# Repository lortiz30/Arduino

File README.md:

Arduino
=======

This repository is for my personal  arduino work

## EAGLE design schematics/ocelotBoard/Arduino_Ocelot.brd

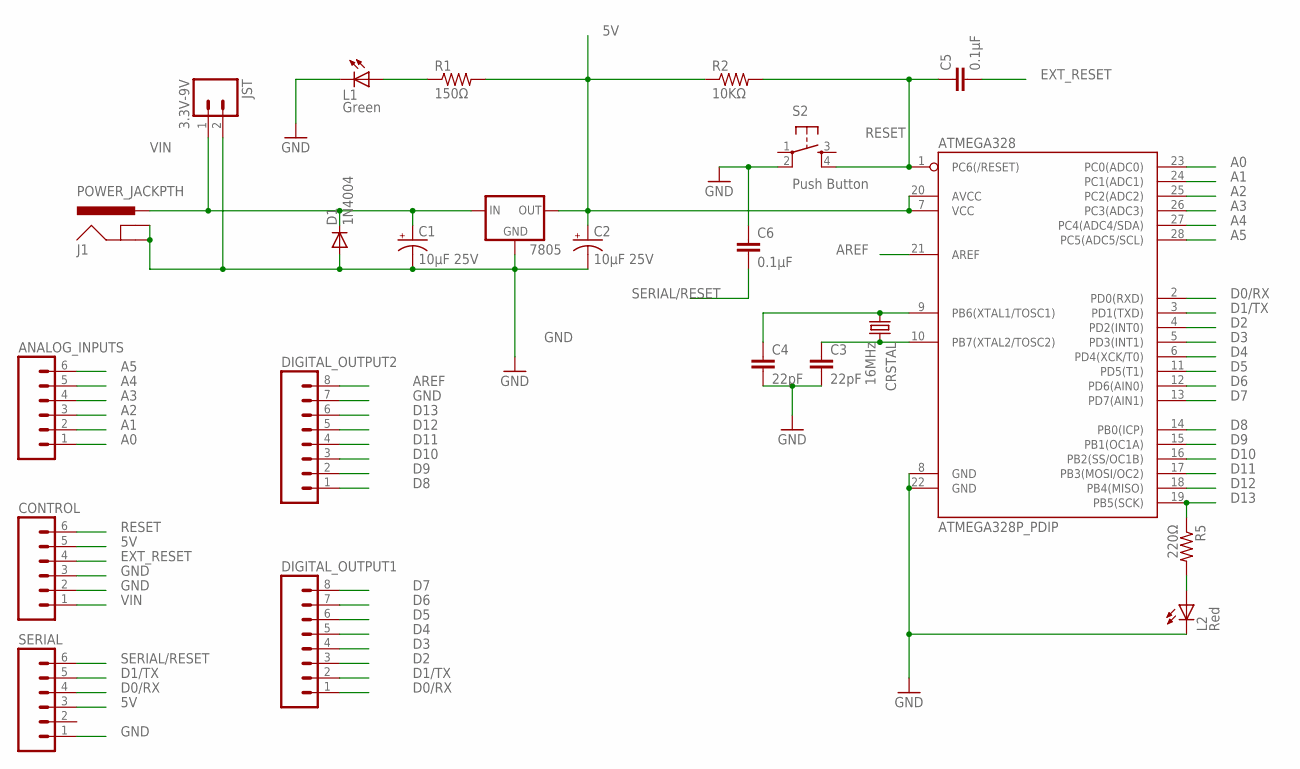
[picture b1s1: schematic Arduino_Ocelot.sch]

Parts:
7805: V_REG_78XXTO-92_UNTESTED; TO-92
ANALOG_INPUTS: M06FEMALE_LOCK; 1X06_FEMALE_LOCK.010
ATMEGA328: ATMEGA328P_PDIP; DIL28-3
C1, C2: 10µF 25V; CPOL-RADIAL-10UF-25V-KIT
C3, C4: 22pF; CAP-PTH-SMALL-KIT
C5, C6: 0.1µF; CAP-PTH-SMALL-KIT
CONTROL: M06FEMALE_LOCK; 1X06_FEMALE_LOCK.010
CRSTAL: 16MHz; HC49US
D1: 1N4004; DIODE-1N4001-KIT
DIGITAL_OUTPUT1, DIGITAL_OUTPUT2: M08NO_SILK; 1X08_NO_SILK
J1: POWER_JACKPTH; POWER_JACK_PTH
JST: 3.3V-9V; JST-2-PTH-VERT
L1: Green; LED3MM
L2: Red; LED3MM
R1: 150Ω; AXIAL-0.4
R2: 10KΩ; AXIAL-0.4
R5: 220Ω; AXIAL-0.4
S2: Push Button; TACTILE-PTH
SERIAL: M06LOCK; 1X06_LOCK

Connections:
5V: 7805.3 (OUT), ATMEGA328.7 (VCC), ATMEGA328.20 (AVCC), C2.1 (+), CONTROL.5, R1.P$2 (2), R2.P$1 (1), SERIAL.3
A0: ANALOG_INPUTS.1, ATMEGA328.23 (PC0(ADC0))
A1: ANALOG_INPUTS.2, ATMEGA328.24 (PC1(ADC1))
A2: ANALOG_INPUTS.3, ATMEGA328.25 (PC2(ADC2))
A3: ANALOG_INPUTS.4, ATMEGA328.26 (PC3(ADC3))
A4: ANALOG_INPUTS.5, ATMEGA328.27 (PC4(ADC4/SDA))
A5: ANALOG_INPUTS.6, ATMEGA328.28 (PC5(ADC5/SCL))
AREF: ATMEGA328.21 (AREF), DIGITAL_OUTPUT2.8
D0/RX: ATMEGA328.2 (PD0(RXD)), DIGITAL_OUTPUT1.1, SERIAL.4
D1/TX: ATMEGA328.3 (PD1(TXD)), DIGITAL_OUTPUT1.2, SERIAL.5
D2: ATMEGA328.4 (PD2(INT0)), DIGITAL_OUTPUT1.3
D3: ATMEGA328.5 (PD3(INT1)), DIGITAL_OUTPUT1.4
D4: ATMEGA328.6 (PD4(XCK/T0)), DIGITAL_OUTPUT1.5
D5: ATMEGA328.11 (PD5(T1)), DIGITAL_OUTPUT1.6
D6: ATMEGA328.12 (PD6(AIN0)), DIGITAL_OUTPUT1.7
D7: ATMEGA328.13 (PD7(AIN1)), DIGITAL_OUTPUT1.8
D8: ATMEGA328.14 (PB0(ICP)), DIGITAL_OUTPUT2.1
D9: ATMEGA328.15 (PB1(OC1A)), DIGITAL_OUTPUT2.2
D10: ATMEGA328.16 (PB2(SS/OC1B)), DIGITAL_OUTPUT2.3
D11: ATMEGA328.17 (PB3(MOSI/OC2)), DIGITAL_OUTPUT2.4
D12: ATMEGA328.18 (PB4(MISO)), DIGITAL_OUTPUT2.5
D13: ATMEGA328.19 (PB5(SCK)), DIGITAL_OUTPUT2.6, R5.P$1 (1)
EXT_RESET: C5.2, CONTROL.4
GND: 7805.1 (GND), ATMEGA328.8 (GND), ATMEGA328.22 (GND), C1.2 (-), C2.2 (-), C3.2, C4.2, C6.1, CONTROL.2, CONTROL.3, D1.A, DIGITAL_OUTPUT2.7, J1.GND, J1.GNDBREAK, JST.2, L1.K (C), L2.K (C), S2.2, SERIAL.1
unnamed: L1.A, R1.P$1 (1)
unnamed: ATMEGA328.10 (PB7(XTAL2/TOSC2)), C3.1, CRSTAL.2
unnamed: L2.A, R5.P$2 (2)
PRUEBA: ATMEGA328.9 (PB6(XTAL1/TOSC1)), C4.1, CRSTAL.1
RESET: ATMEGA328.1 (PC6(/RESET)), C5.1, CONTROL.6, R2.P$2 (2), S2.4
SERIAL/RESET: C6.2, SERIAL.6
VIN: 7805.2 (IN), C1.1 (+), CONTROL.1, D1.C, J1.PWR, JST.1

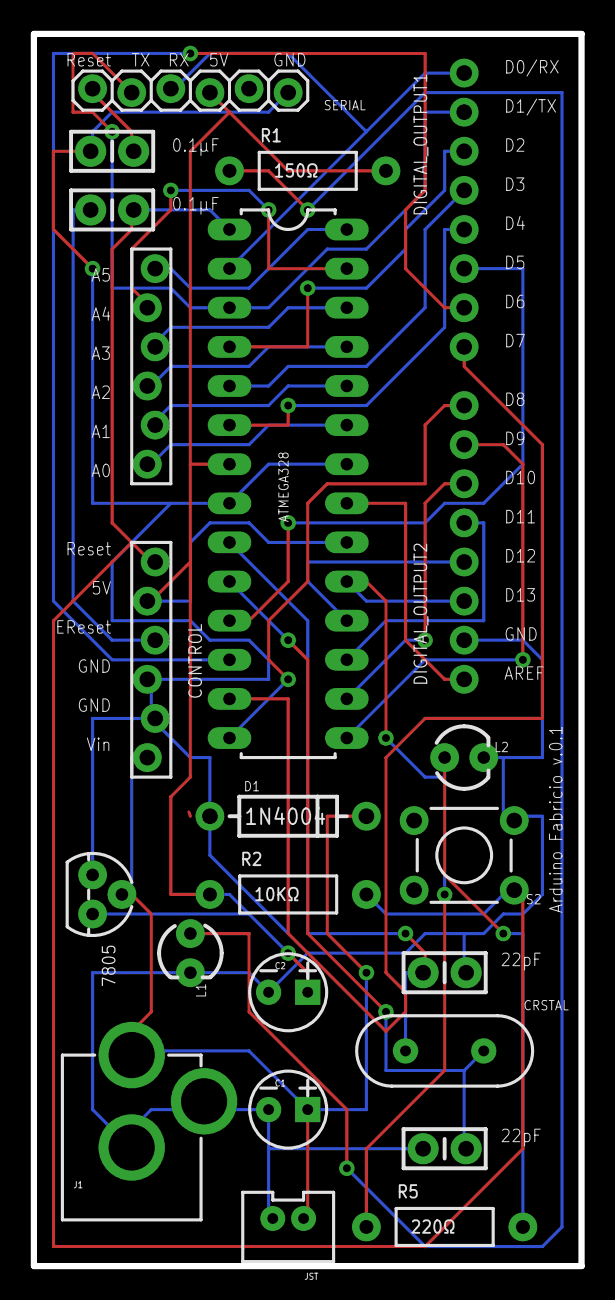
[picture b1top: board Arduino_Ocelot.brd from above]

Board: 2 copper layers, 35.6 x 80.0 mm, 23 parts (0 on the bottom side), 31 nets.

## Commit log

2014-01-29 Added the schematic of my power supply
2014-04-29 Added v.0.1 for arduino ocelot. Also moved the power supply schematic

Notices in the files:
parts and their libraries:
SparkFun-DigitalIC: Licensing: Creative Commons ShareAlike 4.0 International - https://creativecommons.org/licenses/by-sa/4.0
